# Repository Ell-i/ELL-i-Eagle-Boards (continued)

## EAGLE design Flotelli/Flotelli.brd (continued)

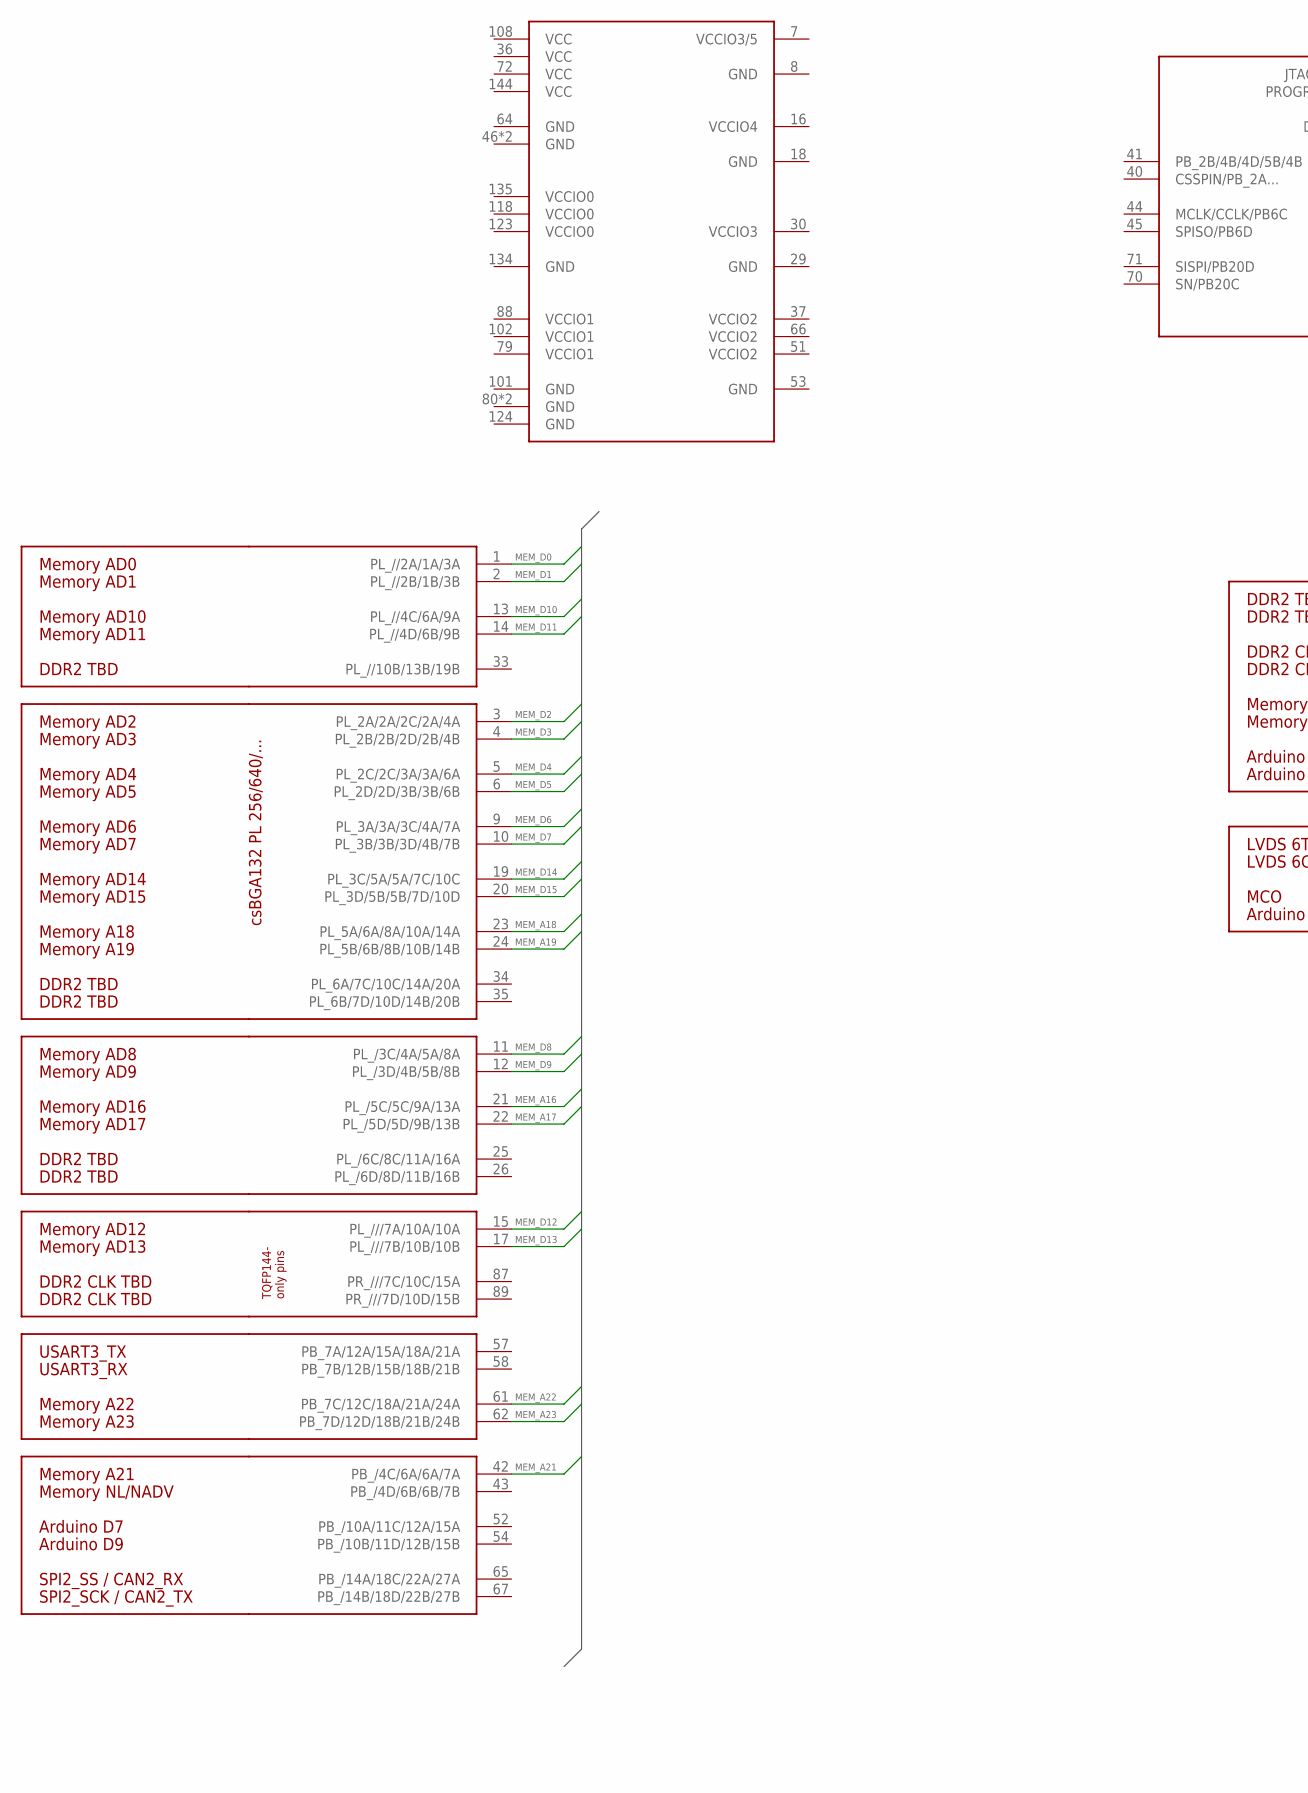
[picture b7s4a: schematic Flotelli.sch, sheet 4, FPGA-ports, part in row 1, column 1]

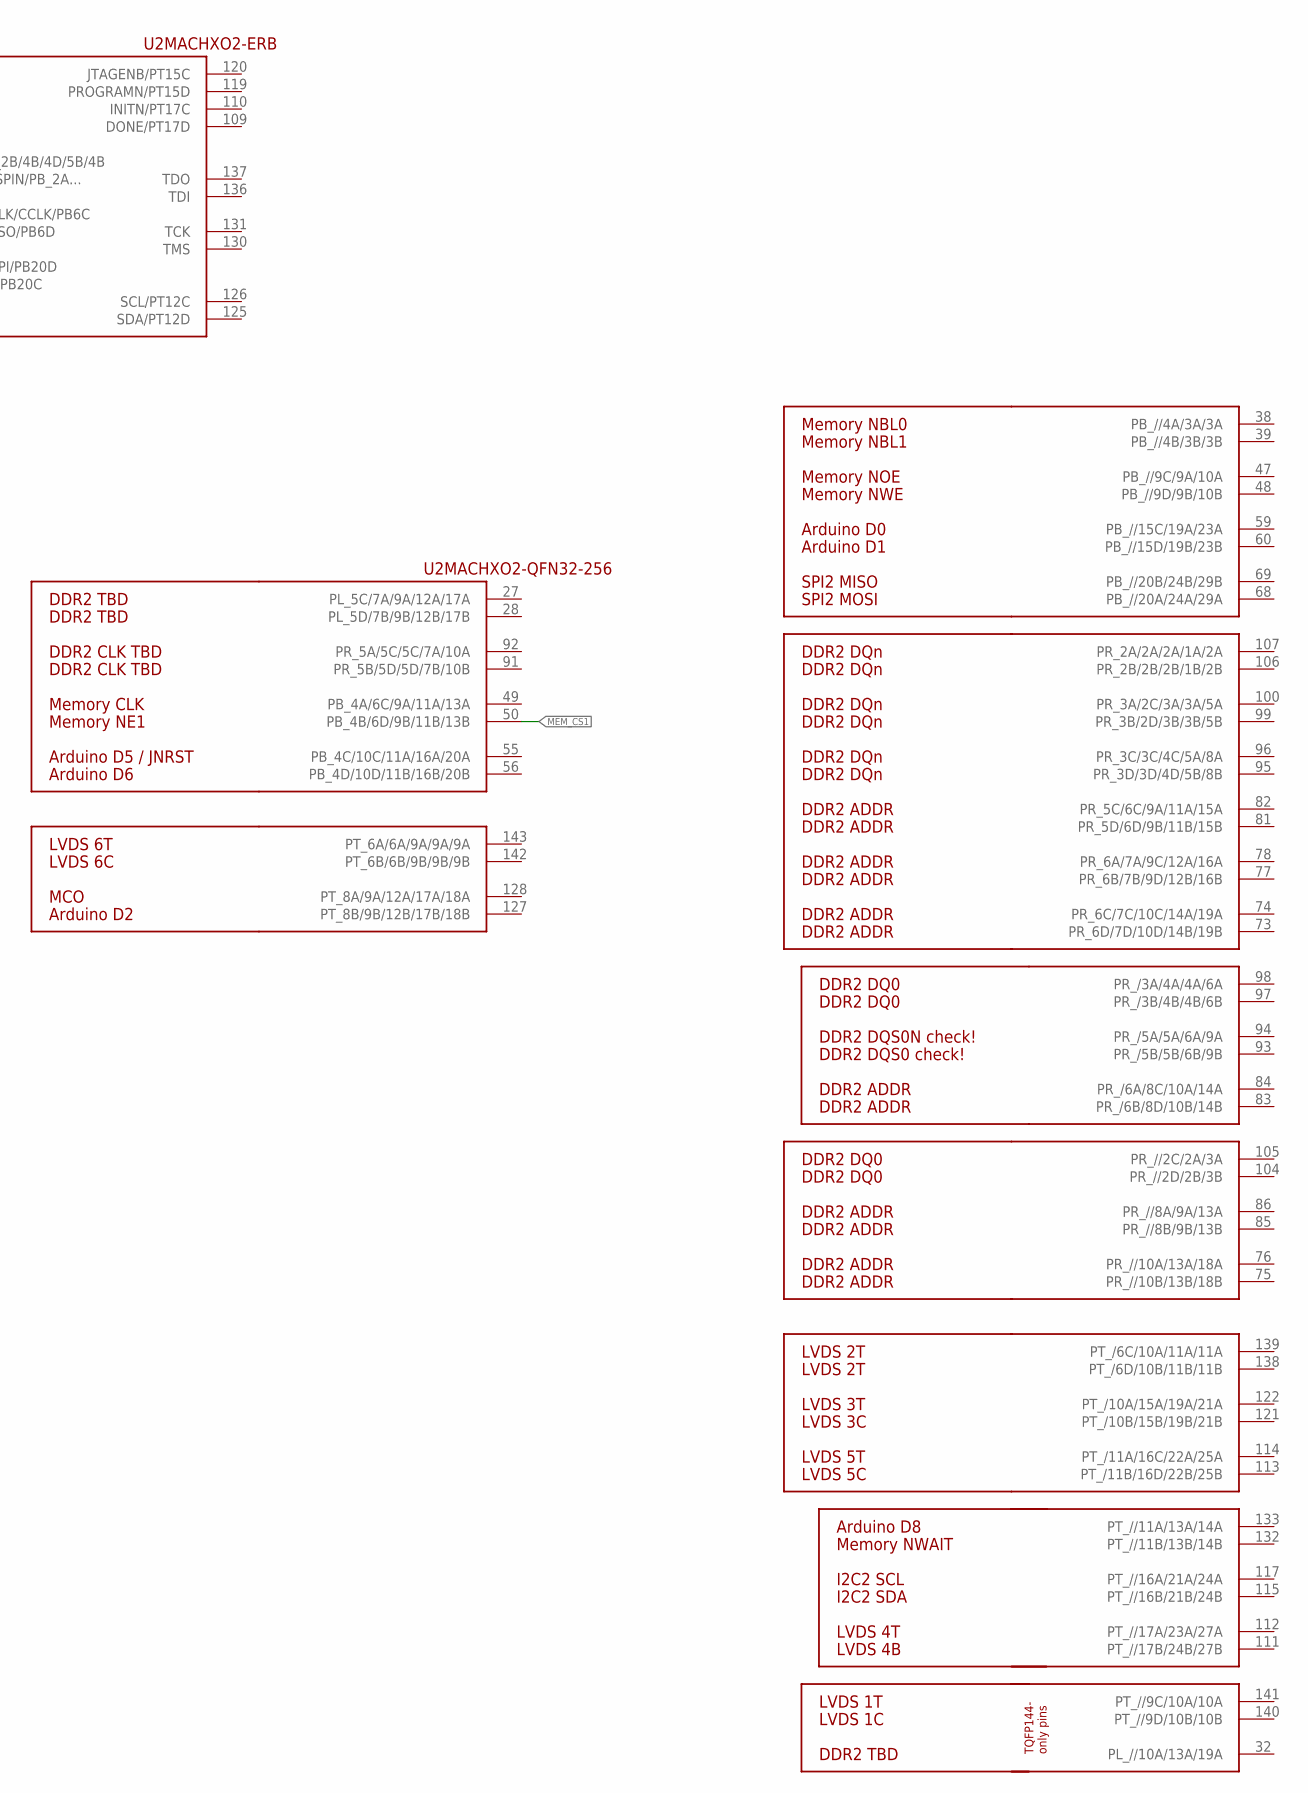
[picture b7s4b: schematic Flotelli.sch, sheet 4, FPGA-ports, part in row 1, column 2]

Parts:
U2: LCMXO2-2000HC-4TG144; TQFP144

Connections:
MEM_A16: U2.21 (PL_/5C/5C/9A/13A); also elsewhere on the board
MEM_A17: U2.22 (PL_/5D/5D/9B/13B); also elsewhere on the board
MEM_A18: U2.23 (PL_5A/6A/8A/10A/14A); also elsewhere on the board
MEM_A19: U2.24 (PL_5B/6B/8B/10B/14B); also elsewhere on the board
MEM_A21: U2.42 (PB_/4C/6A/6A/7A); also elsewhere on the board
MEM_A22: U2.61 (PB_7C/12C/18A/21A/24A); also elsewhere on the board
MEM_A23: U2.62 (PB_7D/12D/18B/21B/24B); also elsewhere on the board
MEM_CS1: U2.50 (PB_4B/6D/9B/11B/13B); also elsewhere on the board
MEM_D0: U2.1 (PL_//2A/1A/3A); also elsewhere on the board
MEM_D1: U2.2 (PL_//2B/1B/3B); also elsewhere on the board
MEM_D2: U2.3 (PL_2A/2A/2C/2A/4A); also elsewhere on the board
MEM_D3: U2.4 (PL_2B/2B/2D/2B/4B); also elsewhere on the board
MEM_D4: U2.5 (PL_2C/2C/3A/3A/6A); also elsewhere on the board
MEM_D5: U2.6 (PL_2D/2D/3B/3B/6B); also elsewhere on the board
MEM_D6: U2.9 (PL_3A/3A/3C/4A/7A); also elsewhere on the board
MEM_D7: U2.10 (PL_3B/3B/3D/4B/7B); also elsewhere on the board
MEM_D8: U2.11 (PL_/3C/4A/5A/8A); also elsewhere on the board
MEM_D9: U2.12 (PL_/3D/4B/5B/8B); also elsewhere on the board
MEM_D10: U2.13 (PL_//4C/6A/9A); also elsewhere on the board
MEM_D11: U2.14 (PL_//4D/6B/9B); also elsewhere on the board
MEM_D12: U2.15 (PL_///7A/10A/10A); also elsewhere on the board
MEM_D13: U2.17 (PL_///7B/10B/10B); also elsewhere on the board
MEM_D14: U2.19 (PL_3C/5A/5A/7C/10C); also elsewhere on the board
MEM_D15: U2.20 (PL_3D/5B/5B/7D/10D); also elsewhere on the board

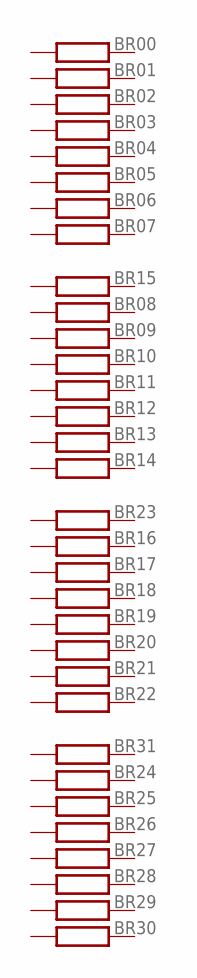
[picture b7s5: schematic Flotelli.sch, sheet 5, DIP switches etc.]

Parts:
BR00, BR01, BR02, BR03, BR04, BR05, BR06, BR07, BR08, BR09, BR10, BR11, BR12, BR13, BR14, BR15, BR16, BR17, BR18, BR19, BR20, BR21, BR22, BR23, BR24, BR25, BR26, BR27, BR28, BR29, BR30, BR31: 100; R0603

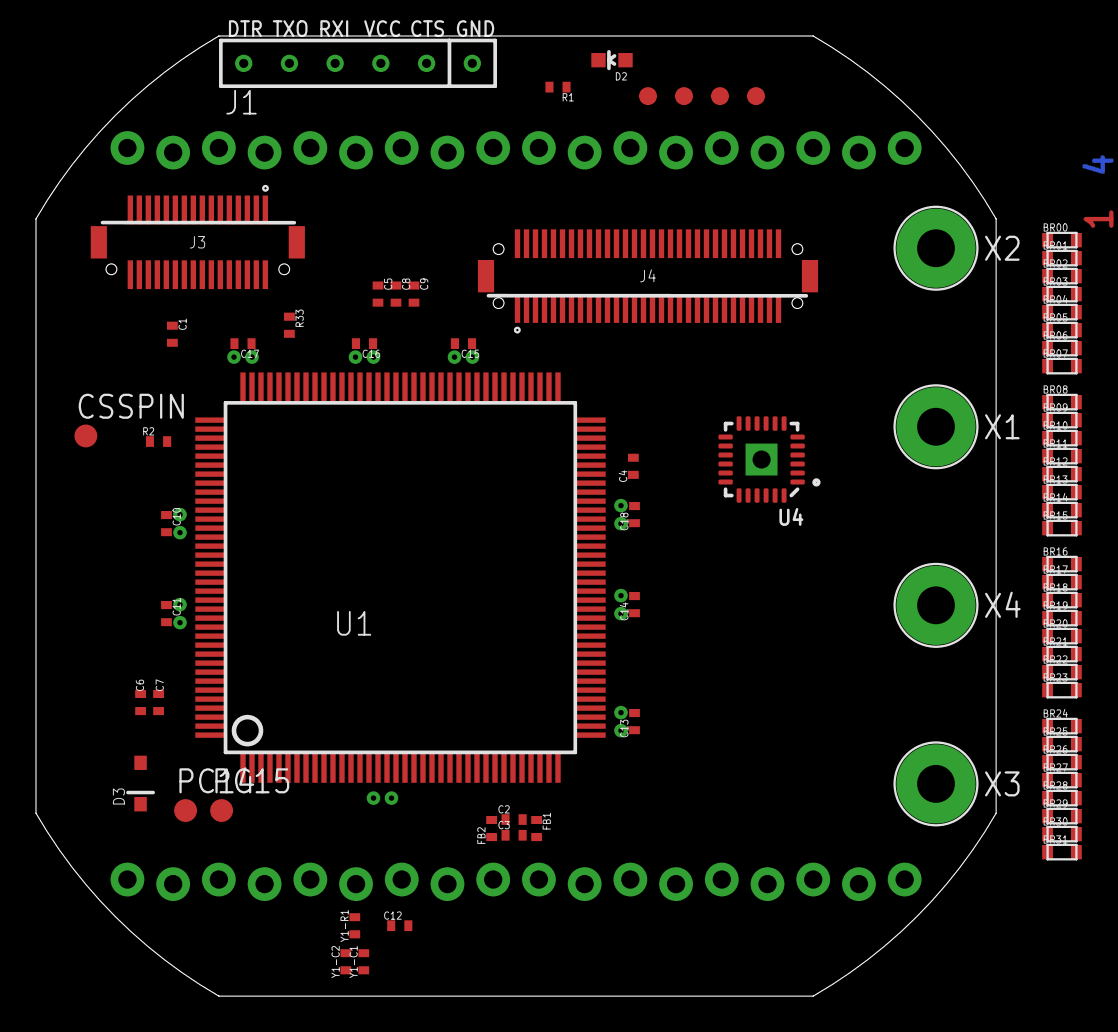
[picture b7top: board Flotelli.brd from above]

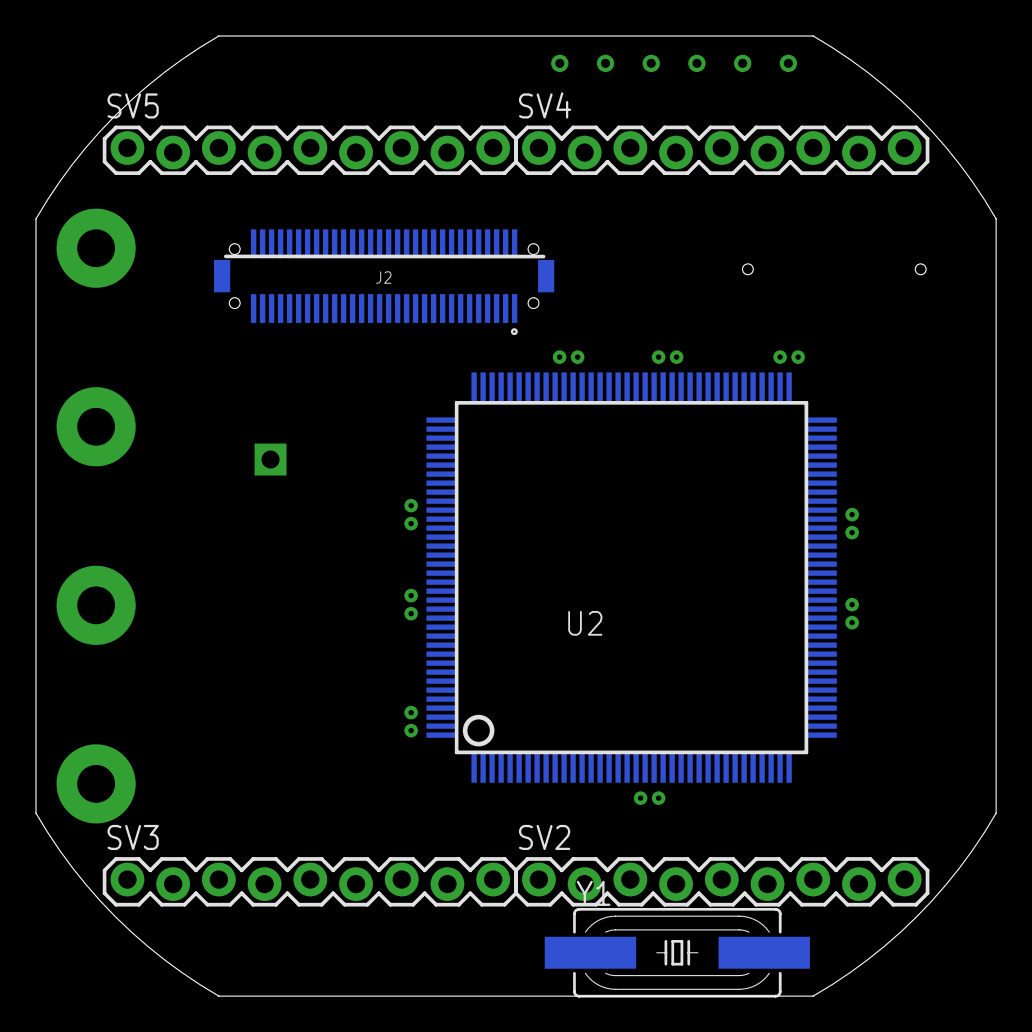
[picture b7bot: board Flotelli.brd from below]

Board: 4 copper layers, 53.3 x 53.3 mm, 101 parts (7 on the bottom side), 69 nets.

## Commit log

2013-04-11 First version of the code
2013-04-16 Ell-i-proto.sch: After running Elli-proto.bom.scr
2013-04-16 Ell-i-proto.sch: Manual edits to place components
2013-04-16 Ell-i-proto.sch: Updated with Timo
2013-04-16 Ell-i-proto.sch: Nets added with a script
2013-04-17 Removed some long wires.
2013-04-17 Removed more wires.
    Fixed missing GNDI in SPI connector.
2013-04-17 Removed more wires. Modified schematics layout.
2013-04-19 Now in three sheets. Still haven't made Timo's changes to this.
2013-04-20 Moved a few parts to clean up
2013-04-20 Add ell-i.lbr
2013-04-21 Minor changes.
2013-04-21 > - U3 ja U4 pinnijärjestys on muuttunut
    Korjattu lbr:ään ja skemaan.
    > - D14 pinnijärjestys muuttunut
    Se oli mielestäni jo oikein sekä lbr:ssä ja skemassa. Tarkistin datasheetistä. Katsokaa nyt tekin.
    > - Uusi Juotostäplä Arduino PWR VIN
    En löytänyt. Mihin tämän siis pitäisi tulla?
    > - J10 vaihtoehtoinen liitin
2013-04-22 library updates, initial state for board, with Arduino Due outline in place
2013-04-22 Due connectors in Due positions, some drafting for other compos
2013-04-22 Timo's BOM added as master BOM doc from now on
2013-04-22 mounting holes, S1 & FTDI conn updated, drafting the placements & GND area, etc
2013-04-22 drafting still, most components inside board edges, and T2 still on left edge
2013-04-22 rearrangement, T2 no more on the edge. Switch in 'location B', LEDs on the corner, etc
2013-04-22 design rules added and applied to brd
2013-04-23 pushbutton and power LED to the right edge, some more drafting
2013-04-23 component placement closer to reality..
2013-04-23 mount fiducial added
2013-04-24 drafting the gnd/power planes in inner layers, some routing, ADCs etc
2013-04-26 all lines somehow routed and seem to fit to the board, some parts updated, etc
2013-04-26 net class & track width updates
2013-04-28 gnd planes optimized etc
2013-04-28 bugfix..
2013-04-28 dru update
2013-04-28 bottom layer filled, DRC nags handled, etc
2013-04-29 renders added
2013-04-30 yet more optimization
2013-04-30 pcb side drawing updates
2013-04-30 optimizations again, some silks to _tsilk layer
2013-04-30 library update
2013-05-02 Changed 1x6 pinstrip to an FTDI-connector component.
    Changed middle layer wires with outer layer wires:
    - Under T1
    - Left of U6
    Optimized away vias for J2 and J4 pins.
    Other optimizations.
2013-05-03 Bom updates from PV and TKJ
2013-05-04 Comments and limitations from PV and PNR applied, generic clearances increased to 0.2mm
2013-05-04 plane optimizations, diode marks & pin1:s to tsilk, jumpers named
2013-05-04 J6 text was not saved..
2013-05-04 updated renders
2013-05-07 final touches for review state
2013-05-07 review state
2013-05-12 0402 pads widened a bit, cream layer bugfix (now 1:1, was something else in DRC settings)
2013-05-14 proto v1.0
2013-05-14 last changes for the final proto 1.0
2013-11-15 Added DF12 connectors.
2013-11-15 Removed DF12 copies with Tinyduino names.
2013-11-22 Horrible Fredi model RR throttle
2013-11-22 Simple switch panel
2013-11-22 Ell-i 2
2013-11-22 Ell-i library
2013-12-11 Add hand-crafted eagle.epf to Ellduino to make a project out of it
2013-12-11 Moved Ell-duino files to the Ell-duino subdirectory, as a preparation to add more boards to this repo.
2013-12-11 Remove unused example files from Flotelli
2013-12-11 Rename Ell-i-2.* to Flotelli.* in Flotelli
2013-12-11 Add initial subdirectory README.md files
2013-12-11 Add hand-crafted eagle.epf to Flotelli
2013-12-13 Add and update READMEs
2013-12-13 Add PoElli-at, a 802.3at power supply board
2013-12-13 Add Eagle DESCRIPTION
2013-12-13 Rename subfolder READMEs to DESCRIPTIONs, for Eagle
2013-12-14 Update Flotelli
2013-12-14 Add .gitignore
2013-12-15 Replaced FTDI header with a new one
2013-12-17 Replaces the 6-pin female header on Flotelli
2013-12-21 Renamed PoElli-at project to simply PoElli. It will contain several PoE boards
2014-01-11 Store first PoEll-i-at board revision on a different name
2014-01-11 Add pin order table in Apple Numbers format
2014-01-11 Make all columns visible in the pin table
2014-01-11 Add first version of pin order commit script
2014-01-11 Add pin order also in CSV for easier viewing
2014-01-11 Added one pin to FPGA in the pin order
2014-01-13 Update the PinOrder table, both CSV and Numbers formats
2014-01-14 Update PinOrder
2014-01-14 Add PinOrder in Excel format (read only recommended)
2014-01-22 Added ENC624J600
2014-01-23 Added RC-snubber to bridge rectifier
2014-01-23 Added RC-snubber value
2014-01-25 Added component values around flyback
2014-01-27 Changed test point library
2014-01-28 Added external power connection
2014-01-28 Add first version of Baselli board; very much work in progress
2014-01-28 Changes to Baselli. Still very much WIP
2014-01-30 Add first version of ELL-i header to Baselli. WIP.
2014-01-31 Add bus labels etc to Baselli
2014-02-01 Update Baselli. Still WIP.
2014-02-01 Minor fixes to Baselli
2014-02-04 Changed Baselli DIP switches to smaller ones
2014-02-04 Small mostly cosmetic changes to Baselli
2014-02-05 Another commit of small mostly cosmetic changes to Baselli
2014-02-07 Change JTAG connector and PIN order for STM32F PB1, PB4 and PB8
2014-02-14 Add mux
2014-02-25 Add placeholder components
2014-02-26 Add eagle.epf to Baselli
2014-02-27 Adding WS2812B to Baselli board schematics
2014-02-27 Add resistors R10 and R11 to Baselli
2014-02-27 Adding WS2812B RGB LED to Baselli. Begining Arduelli schematic
2014-03-04 Add signal naming to PinOrder
2014-03-04 Update the other formats of PinOrder
2014-03-05 Initial commit for power arbitration circuit without any isolation
2014-03-07 Update libraries & Small changes to Baselli as agreed on March 5
2014-03-07 Replaced DIP switches with series resistors in Baselli
2014-03-07 Small enhancements to Baselli
2014-03-07 Add dip switch & clean up serial programming circuit in Baselli
2014-03-07 Replace Frames in Baselli to the new A4 landscape version
2014-03-07 Update and add wiring for ELL-i and RasPi connectors
2014-03-08 Cleanup PoElli-at aka Piwelli
2014-03-08 Small fixes to PoElli
2014-03-09 Flotelli pins defined per the latest pin order table.
    There are still some errors in the table. We will fix them next.
    Also has Flotelli brd, very preliminary.
2014-03-09 Small fixes to Baselli
2014-03-09 Correct pins MEM_D11-MEM_D14 in PinOrder
2014-03-12 Add file
2014-03-12 Update connector connections
2014-03-21 Import fixed testpoints
2014-03-23 Add a temp file for PoElli renumbering
2014-03-23 Fix PoElli renumbering file
2014-03-23 Move BAV20WS to Ell-i-DiscreteSemi.lbr
2014-03-23 Manually renamed PoElli components other than R,C,D
2014-03-23 Renamed R,C,D in PoElli
2014-03-23 Fix previous commit screwups + cleanups to PoElli
2014-03-25 Cleanups to PoElli schematics
2014-03-25 Further cleanups and add components to PoElli schematics
2014-03-25 Small cleanups to PoElli
2014-03-26 Added an example schematics and board for DIN49073 PCB. Idea is that you can add one outline component which doesn't have any pads and then add, in this case, two pads components totalling 20 pins. T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
2014-03-26 Arrange PoElli testpoints
2014-03-27 BasElli review fixes
2014-03-27 Baselli cleanups
2014-03-27 Change to ENC424J600 & cleanups in PoElli
2014-03-27 Initial layout for PoElli
2014-03-27 Minor mods to PoElli initial layout
2014-03-28 Add rtc crystal
2014-03-29 Review changes to PoElli-at
2014-03-29 Add board to Baselli
2014-03-29 Add first version of Nucleo PoE shield
2014-03-29 Add 32 kHz oscillator to .brd & rename
2014-03-29 Fixups and renumbering in Baselli
2014-03-29 Renumbering & initial routing on Baselli
2014-03-29 Mechanical design
2014-03-30 Remove excess punchdown connector from Baselli
2014-03-30 Work on PoElli-at
2014-03-30 More work on Nucleo
2014-04-01 Move Hirose DF12 locations as agreed yesterday
2014-04-03 Preliminary work on Baselli
2014-04-03 Update libraries on PoElli
2014-04-06 Add first version of mechanics variations
2014-04-07 More preliminary work on Baselli
2014-04-07 Baselli: Ripof all trials, move components as learned in the lesson
2014-04-08 Changes to PoElli-RasPi-offset-RJ45 from today's meeting
2014-04-08 Changes to PoElli-Nucleo-short from today's meeting
2014-04-08 Update DIN49073 component placement script
2014-04-08 Changes to Baselli from today's meeting
2014-04-08 Update Nucleo shield construction for Mechanics/PoElli-Nucleo-mechanics-short.{brd,sch}
2014-04-09 Move transformers in PoEll-i RasPi mechanics model
2014-04-09 mechanics test panel draft 1
2014-04-10 final touches & set 0.5mm clearance from copper pour to pads
2014-04-11 Preliminary version of Arduelli
2014-04-11 Update PoElli/Mechanics non-produced boards with new library components
2014-04-11 Move components in Baselli layout, anticipating autorouter
2014-04-12 Replace RJ-45 connector in PoE-at & relocate transformers
2014-04-12 Work on RasPi PoElli
2014-04-13 Preliminary work on PoElli Nucleo layout
2014-04-13 Work on PoElli Nucleo
2014-04-13 Work on PoElli RasPi
2014-04-14 Small fix to PoElli-Nucleo
2014-04-15 Update Nucleo header origin to the center of the component
2014-04-15 Update RasPi outline & connector
2014-04-15 Add network classes to PoElli
2014-04-16 Added layers. Moved parts.
    Per discussion between Pekka and Antti.
2014-04-17 Add filter capacitors for Mach XO2 and initial routing for power
2014-04-17 Add SJ17,18 to Baselli for SMT32L063 compatibility
2014-04-17 Changed wire classes in Baselli
2014-04-17 Tweaking Baselli, with diminsihed returns
2014-04-18 Changed the LCMXO2 package to the one with vias.
    Now it routes.
2014-04-18 Arduelli with the crystal and other connections
2014-04-18 Spreadsheet for Crystal value calculator
2014-04-19 Fixed the RJ45 issue in layout. Minor fixes.
2014-04-20 Added pins, nets for Arduino header. Minor fixes.
2014-04-21 Adding connections to the ELL-i bus. Other fixes.
2014-04-21 routing draft v0.2, planes & routes in, optimization to be done..
2014-04-22 Added M2 screw holes. Connections to the ELL-i bus.
2014-04-23 gnd vias, planes etc
2014-04-24 smallest via drill to 0.25mm (was 0.2), + small improvments
2014-04-26 review changes applied
2014-04-26 placement images of the latest drafts
2014-04-26 final tweakings, draft v0.9
2014-04-27 v1.0
2014-04-27 renders of the 1.0
2014-05-04 Added Junction to the Power arbitration circuit
2014-05-07 Added JTAG power logic+Modified Power Arbiter gnds
2014-05-09 Fixes to Schematic for connec. problems in layout
2014-05-10 Proper naming of supply nets to represent multiple voltage symbols
2014-05-29 Changed the values of the capacitor on NCP1117
2014-05-29 Block diagram of Arduelli
2014-06-27 Arduelli board - preliminary version
2014-06-30 Remove R10
2014-07-01 Add PoElli-Nucleo.brd to preserve backannotation
2014-07-01 Fix broken net between C21 and D3/R16
2014-07-04 Preliminary version of Arduelli board - 2
2014-07-10 Fix mistakes from first prototype round
2014-07-21 rev 3 DRC ok
2014-07-28 Preliminary version of Arduelli board - 3
2014-08-18 rev 0.3
2014-08-22 PoElli 0.4 Schema, tentative layout
2014-08-22 tentative layout
2014-08-26 Layout, functional blocks placed down
2014-08-27 Component placement almost ready
2014-09-01 DC/DC layout except planes
2014-09-02 Fix SPI pin order
2014-09-02 Component placement complete
2014-09-05 component placement, planes final.
2014-09-05 Layout complete, except silkscreen.
2014-09-08 Copper layers, complete, DRC ok. Silkscreen has to be adjusted.
2014-09-14 Silkscreen ok
2014-09-21 PoELLi 1.0
2014-10-03 Fix Bridge rectifier connection
2014-10-29 Lower value of interrupt resistor to 24k9
2014-10-29 Add pdf printouts of schematic and board
